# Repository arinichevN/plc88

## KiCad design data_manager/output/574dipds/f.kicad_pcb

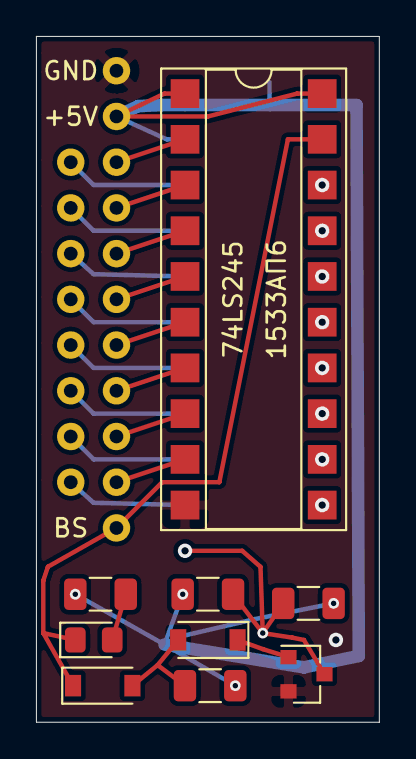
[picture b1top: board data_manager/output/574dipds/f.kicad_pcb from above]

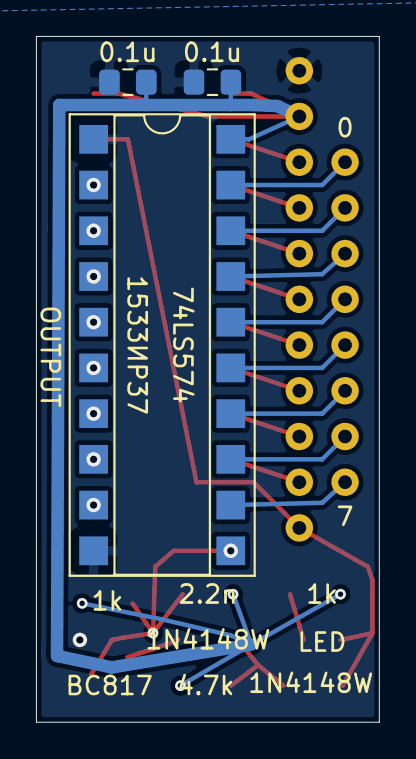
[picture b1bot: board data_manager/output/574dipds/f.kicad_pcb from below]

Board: 2 copper layers, 19.0 x 38.1 mm, 13 parts (3 on the bottom side), 31 nets.

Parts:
C1, C2: 0.1u; C_0805_2012Metric_Pad1.15x1.40mm_HandSolder
C3: 2.2n; C_1206_3216Metric
D1, D2: 1N4148W; D_SOD-123
D3: LED; LED_0805_2012Metric_Pad1.15x1.40mm_HandSolder
J1: data_manager_i; data_manager_im
Q1: BC817; SOT-23
R3: 4.7k; R_1206_3216Metric
R4, R5: 1k; R_1206_3216Metric
U1: 74LS245; DIP-20_W7.62mm_SMDSocket_SmallPads
U2: 74LS574; DIP-20_W7.62mm_SMDSocket_SmallPads

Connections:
+5V: C1.2, C2.2, C3.1, J1.18, R3.1, R4.1, R5.2, U1.1, U1.20, U2.20
BD0: U1.18, U2.2
BD1: U1.17, U2.3
BD2: U1.16, U2.4
BD3: U1.15, U2.5
BD4: U1.14, U2.6
BD5: U1.13, U2.7
BD6: U1.12, U2.8
BD7: U1.11, U2.9
BS: D1.1, D3.1, J1.19, U1.19
D0: J1.2, U1.2
D1: J1.4, U1.3
D2: J1.6, U1.4
D3: J1.8, U1.5
D4: J1.10, U1.6
D5: J1.12, U1.7
D6: J1.14, U1.8
D7: J1.16, U1.9
GND: C1.1, C2.1, J1.17, Q1.2, U1.10, U2.1, U2.10
unnamed: D1.2, D2.2, R3.2
unnamed: D2.1, Q1.1
unnamed: D3.2, R5.1
OPL0: J1.1, U2.19
OPL1: J1.3, U2.18
OPL2: J1.5, U2.17
OPL3: J1.7, U2.16
OPL4: J1.9, U2.15
OPL5: J1.11, U2.14
OPL6: J1.13, U2.13
OPL7: J1.15, U2.12
TCLK: C3.2, Q1.3, R4.2, U2.11

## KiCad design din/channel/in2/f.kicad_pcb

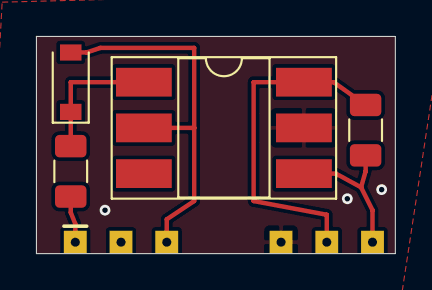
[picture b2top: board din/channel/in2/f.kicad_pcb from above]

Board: 2 copper layers, 19.9 x 12.1 mm, 5 parts (0 on the bottom side), 6 nets.

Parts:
D1: 1N4148W; D_SOD-123
J1: dio_channel_i; dio_channel_im
R1: 4.7k; R_1206_3216Metric
R2: 270; R_1206_3216Metric
U1: H11L1; DIP-6_W8.89mm_SMDSocket_LongPads

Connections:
+5V: J1.5, R2.2, U1.6
GND: J1.4, U1.5
IN: J1.1, R1.2
unnamed: D1.1, R1.1, U1.1
OUT: J1.6, R2.1, U1.4
VINM: D1.2, J1.3, U1.2

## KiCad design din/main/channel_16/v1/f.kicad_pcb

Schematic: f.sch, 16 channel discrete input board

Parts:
C1, C2: 0.1u; C_0805_2012Metric_Pad1.15x1.40mm_HandSolder
D1: SR1; LED_0805_2012Metric_Pad1.15x1.40mm_HandSolder
D2: SR0; LED_0805_2012Metric_Pad1.15x1.40mm_HandSolder
D3, D4, D5, D6, D7, D8, D9, D10, D11, D12, D13, D14, D15, D16, D17, D18: 1N4148W; D_SOD-123
J1: fm16_i; fm16_im
J2, J3: wrs_i
J4: bus_i; bus_im
J5: selector4_i
J6: power_+5V; power_i
R1, R2, R5, R6, R9, R10, R13, R14, R17, R18, R21, R22, R25, R26, R29, R30: 3.3k; R_1206_3216Metric_Pad1.42x1.75mm_HandSolder
R3, R4, R7, R8, R11, R12, R15, R16, R19, R20, R23, R24, R27, R28, R31, R32: 4.7k; R_1206_3216Metric_Pad1.42x1.75mm_HandSolder
R33, R34: 1k; R_1206_3216Metric_Pad1.42x1.75mm_HandSolder
U1, U2, U3, U4, U6, U7, U8, U9, U10, U11, U12, U13, U15, U16, U17, U18: LTV-357T; SO-4_4.4x3.6mm_P2.54mm
U21, U22: 74LS245; DIP-20_W8.89mm_SMDSocket_LongPads

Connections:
+5V: C1.2, C2.2, J2.6 (+5V), J3.6 (+5V), J5.1 (+5V), J6.2, R1.2, R2.2, R5.2, R6.2, R9.2, R10.2, R13.2, R14.2, R17.2, R18.2, R21.2, R22.2, R25.2, R26.2, R29.2, R30.2, R33.1, R34.1, U21.20 (VCC), U22.20 (VCC)
A0: J4.5 (A0), J5.2 (A0)
A1: J4.7 (A1), J5.3 (A1)
A2: J4.9 (A2), J5.4 (A2)
A3: J4.11 (A3), J5.5 (A3)
A4: J4.13 (A4), J5.6 (A4)
A5: J4.15 (A5), J5.7 (A5)
A6: J4.17 (A6), J5.8 (A6)
A7: J4.19 (A7), J5.9 (A7)
CLK: J4.21 (CLK), J4.22 (CLK), J5.10 (CLK)
D0: J4.6 (D0), U21.2 (A0), U22.2 (A0)
D1: J4.8 (D1), U21.3 (A1), U22.3 (A1)
D2: J4.10 (D2), U21.4 (A2), U22.4 (A2)
D3: J4.12 (D3), U21.5 (A3), U22.5 (A3)
D4: J4.14 (D4), U21.6 (A4), U22.6 (A4)
D5: J4.16 (D5), U21.7 (A5), U22.7 (A5)
D6: J4.18 (D6), U21.8 (A6), U22.8 (A6)
D7: J4.20 (D7), U21.9 (A7), U22.9 (A7)
GND: C1.1, C2.1, J1.21 (GND), J1.22 (GND), J1.23 (GND), J1.24 (GND), J1.25 (GND), J2.1 (GND), J3.1 (GND), J4.1 (GND), J4.2 (GND), J4.27 (GND), J4.28 (GND), J5.11 (GND), J6.3, U1.3, U2.3, U3.3, U4.3, U6.3, U7.3, U8.3, U9.3, U10.3, U11.3, U12.3, U13.3, U15.3, U16.3, U17.3, U18.3, U21.1 (A->B), U21.10 (GND), U22.1 (A->B), U22.10 (GND)
GND0_7: D3.2 (A), D4.2 (A), D5.2 (A), D6.2 (A), D7.2 (A), D8.2 (A), D9.2 (A), D10.2 (A), J1.17 (VM0_7), U1.2, U3.2, U6.2, U8.2, U10.2, U12.2, U15.2, U17.2
GND8_15: D11.2 (A), D12.2 (A), D13.2 (A), D14.2 (A), D15.2 (A), D16.2 (A), D17.2 (A), D18.2 (A), J1.20 (VM8_15), U2.2, U4.2, U7.2, U9.2, U11.2, U13.2, U16.2, U18.2
IN0: J1.1 (L0), R3.1
IN1: J1.2 (L1), R7.1
IN2: J1.3 (L2), R11.1
IN3: J1.4 (L3), R15.1
IN4: J1.5 (L4), R19.1
IN5: J1.6 (L5), R23.1
IN6: J1.7 (L6), R27.1
IN7: J1.8 (L7), R31.1
IN8: J1.9 (L8), R4.1
IN9: J1.10 (L9), R8.1
IN10: J1.11 (L10), R12.1
IN11: J1.12 (L11), R16.1
IN12: J1.13 (L12), R20.1
IN13: J1.14 (L13), R24.1
IN14: J1.15 (L14), R28.1
IN15: J1.16 (L15), R32.1
INL0: R1.1, U1.4, U21.18 (B0)
INL1: R5.1, U3.4, U21.17 (B1)
INL2: R9.1, U6.4, U21.16 (B2)
INL3: R13.1, U8.4, U21.15 (B3)
INL4: R17.1, U10.4, U21.14 (B4)
INL5: R21.1, U12.4, U21.13 (B5)
INL6: R25.1, U15.4, U21.12 (B6)
INL7: R29.1, U17.4, U21.11 (B7)
INL8: R2.1, U2.4, U22.18 (B0)
INL9: R6.1, U4.4, U22.17 (B1)
INL10: R10.1, U7.4, U22.16 (B2)
INL11: R14.1, U9.4, U22.15 (B3)
INL12: R18.1, U11.4, U22.14 (B4)
INL13: R22.1, U13.4, U22.13 (B5)
INL14: R26.1, U16.4, U22.12 (B6)
INL15: R30.1, U18.4, U22.11 (B7)
unnamed: D1.2 (A), R33.2
unnamed: D2.2 (A), R34.2
unnamed: D3.1 (K), R3.2, U1.1
unnamed: D4.1 (K), R7.2, U3.1
unnamed: D5.1 (K), R11.2, U6.1
unnamed: D6.1 (K), R15.2, U8.1
unnamed: D7.1 (K), R19.2, U10.1
unnamed: D8.1 (K), R23.2, U12.1
unnamed: D9.1 (K), R27.2, U15.1
unnamed: D10.1 (K), R31.2, U17.1
unnamed: D11.1 (K), R4.2, U2.1
unnamed: D12.1 (K), R8.2, U4.1
unnamed: D13.1 (K), R12.2, U7.1
unnamed: D14.1 (K), R16.2, U9.1
unnamed: D15.1 (K), R20.2, U11.1
unnamed: D16.1 (K), R24.2, U13.1
unnamed: D17.1 (K), R28.2, U16.1
unnamed: D18.1 (K), R32.2, U18.1
RD: J2.3 (WR), J3.3 (WR), J4.23 (RD)
S0: J2.4 (S), J5.12 (S0)
S1: J3.4 (S), J5.13 (S1)
SR0: D2.1 (K), J2.5 (SOUT), U21.19 (CE)
SR1: D1.1 (K), J3.5 (SOUT), U22.19 (CE)
VPBUS: J4.3 (+5V), J4.4 (+5V), J4.25 (+5V), J4.26 (+5V), J6.1
WR: J2.2 (WRN), J3.2 (WRN), J4.24 (WR)

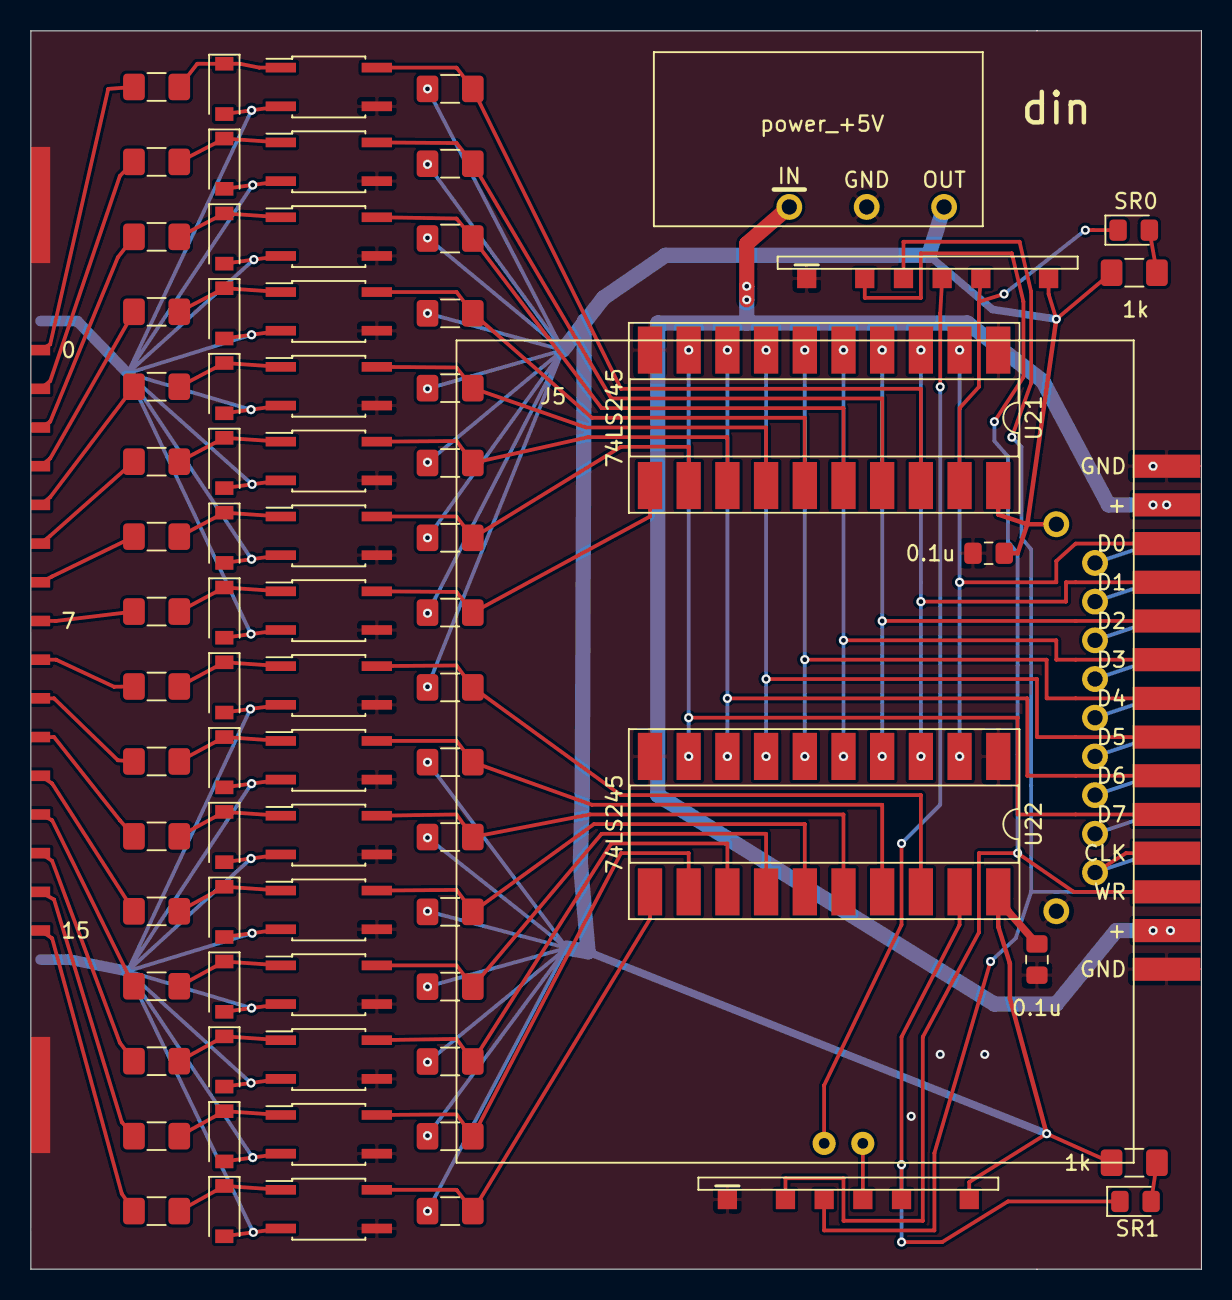
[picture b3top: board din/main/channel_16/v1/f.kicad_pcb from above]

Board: 2 copper layers, 76.8 x 81.3 mm, 78 parts (0 on the bottom side), 78 nets.

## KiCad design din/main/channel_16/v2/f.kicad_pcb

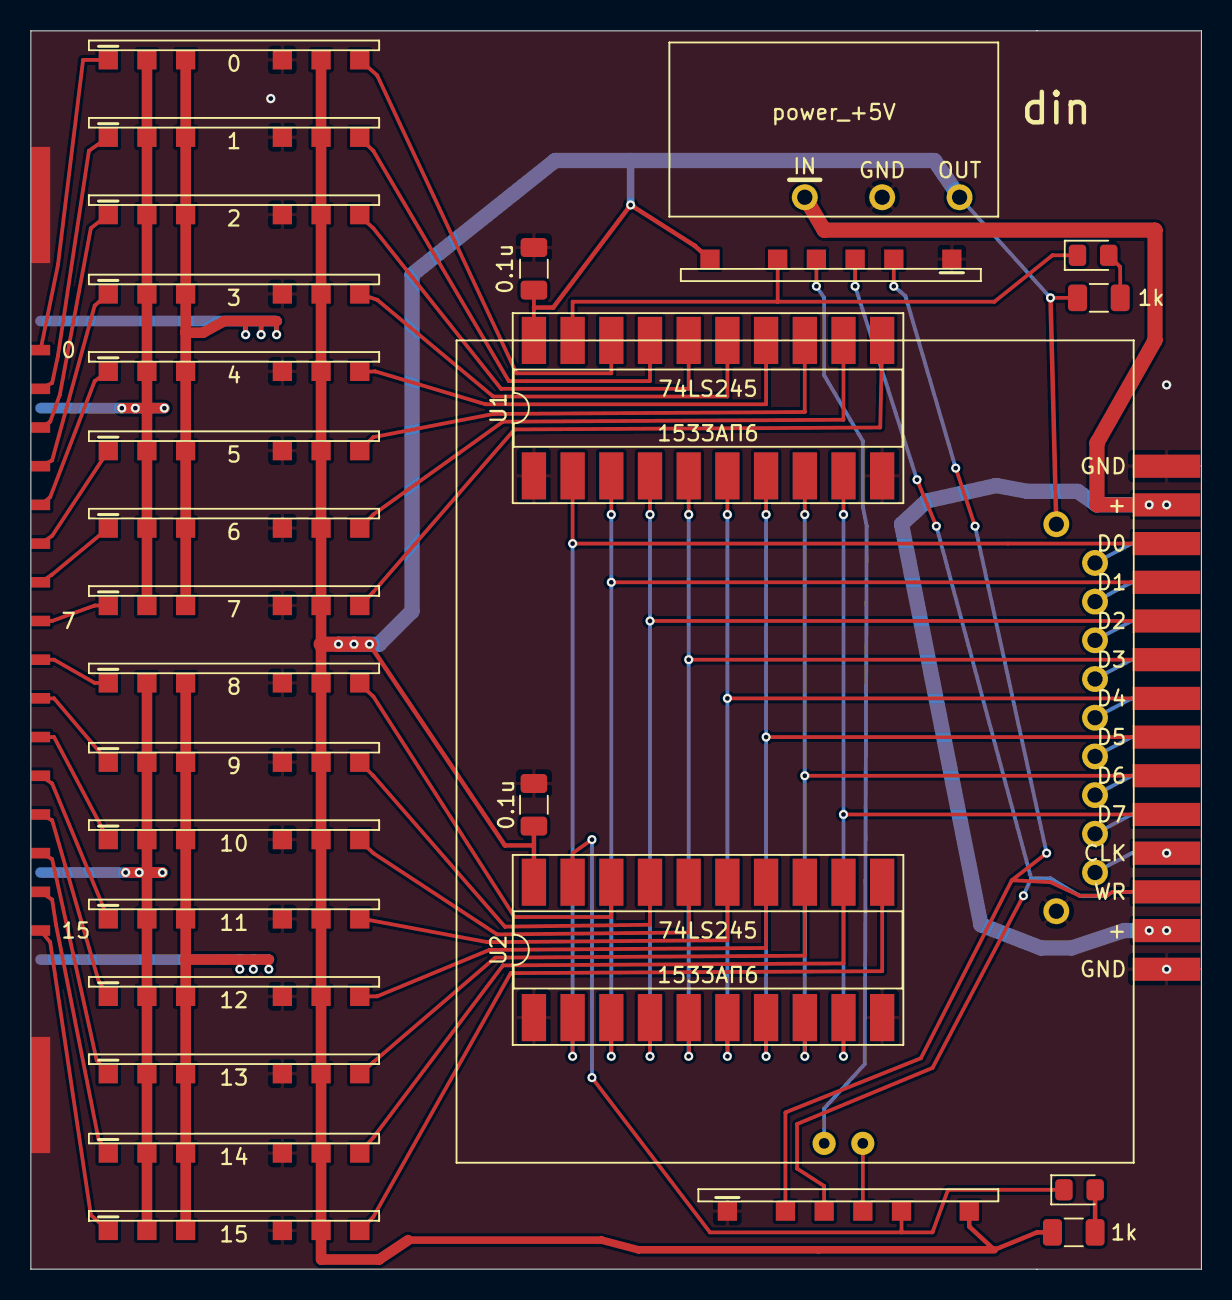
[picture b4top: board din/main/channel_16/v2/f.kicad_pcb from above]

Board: 2 copper layers, 76.8 x 81.3 mm, 30 parts (0 on the bottom side), 64 nets.

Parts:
C1, C2: 0.1u; C_1206_3216Metric
D1, D2: SR0; LED_0805_2012Metric_Pad1.15x1.40mm_HandSolder
J1: fm16_i; fm16_im
J2, J3, J4, J5, J6, J7, J8, J9, J13, J14, J15, J16, J17, J18, J19, J20: dio_channel_i
J10, J21: wrs_i
J11: selector4_i
J12: power_+5V; power_i
J22: bus_i; bus_im
R1, R2: 1k; R_1206_3216Metric
U1, U2: 74LS245; DIP-20_W8.89mm_SMDSocket_LongPads

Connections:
+5V: C1.2, C2.2, J2.5, J3.5, J4.5, J5.5, J6.5, J7.5, J8.5, J9.5, J10.6, J11.1, J12.2, J13.5, J14.5, J15.5, J16.5, J17.5, J18.5, J19.5, J20.5, J21.6, R1.1, R2.1, U1.20, U2.20
A0: J11.2, J22.5
A1: J11.3, J22.7
A2: J11.4, J22.9
A3: J11.5, J22.11
A4: J11.6, J22.13
A5: J11.7, J22.15
A6: J11.8, J22.17
A7: J11.9, J22.19
CLK: J11.10, J22.21, J22.22
D0: J22.6, U1.2, U2.2
D1: J22.8, U1.3, U2.3
D2: J22.10, U1.4, U2.4
D3: J22.12, U1.5, U2.5
D4: J22.14, U1.6, U2.6
D5: J22.16, U1.7, U2.7
D6: J22.18, U1.8, U2.8
D7: J22.20, U1.9, U2.9
GND: C1.1, C2.1, J1.21, J1.22, J1.23, J1.24, J1.25, J2.4, J3.4, J4.4, J5.4, J6.4, J7.4, J8.4, J9.4, J10.1, J11.11, J12.3, J13.4, J14.4, J15.4, J16.4, J17.4, J18.4, J19.4, J20.4, J21.1, J22.1, J22.2, J22.27, J22.28, U1.1, U1.10, U2.1, U2.10
GND0_7: J1.17, J2.3, J3.3, J4.3, J5.3, J6.3, J7.3, J8.3, J9.3
GND8_15: J1.20, J13.3, J14.3, J15.3, J16.3, J17.3, J18.3, J19.3, J20.3
IN0: J1.1, J2.1
IN1: J1.2, J3.1
IN2: J1.3, J4.1
IN3: J1.4, J5.1
IN4: J1.5, J6.1
IN5: J1.6, J7.1
IN6: J1.7, J8.1
IN7: J1.8, J9.1
IN8: J1.9, J13.1
IN9: J1.10, J14.1
IN10: J1.11, J15.1
IN11: J1.12, J16.1
IN12: J1.13, J17.1
IN13: J1.14, J18.1
IN14: J1.15, J19.1
IN15: J1.16, J20.1
INL0: J2.6, U1.18
INL1: J3.6, U1.17
INL2: J4.6, U1.16
INL3: J5.6, U1.15
INL4: J6.6, U1.14
INL5: J7.6, U1.13
INL6: J8.6, U1.12
INL7: J9.6, U1.11
INL8: J13.6, U2.18
INL9: J14.6, U2.17
INL10: J15.6, U2.16
INL11: J16.6, U2.15
INL12: J17.6, U2.14
INL13: J18.6, U2.13
INL14: J19.6, U2.12
INL15: J20.6, U2.11
unnamed: D1.2, R1.2
unnamed: D2.2, R2.2
RD: J10.3, J21.3, J22.23
S0: J10.4, J11.12
S1: J11.13, J21.4
SR0: D1.1, J10.5, U1.19
SR1: D2.1, J21.5, U2.19
V0_7: J1.18, J2.2, J3.2, J4.2, J5.2, J6.2, J7.2, J8.2, J9.2
V8_15: J1.19, J13.2, J14.2, J15.2, J16.2, J17.2, J18.2, J19.2, J20.2
VPBUS: J12.1, J22.3, J22.4, J22.25, J22.26
WR: J10.2, J21.2, J22.24

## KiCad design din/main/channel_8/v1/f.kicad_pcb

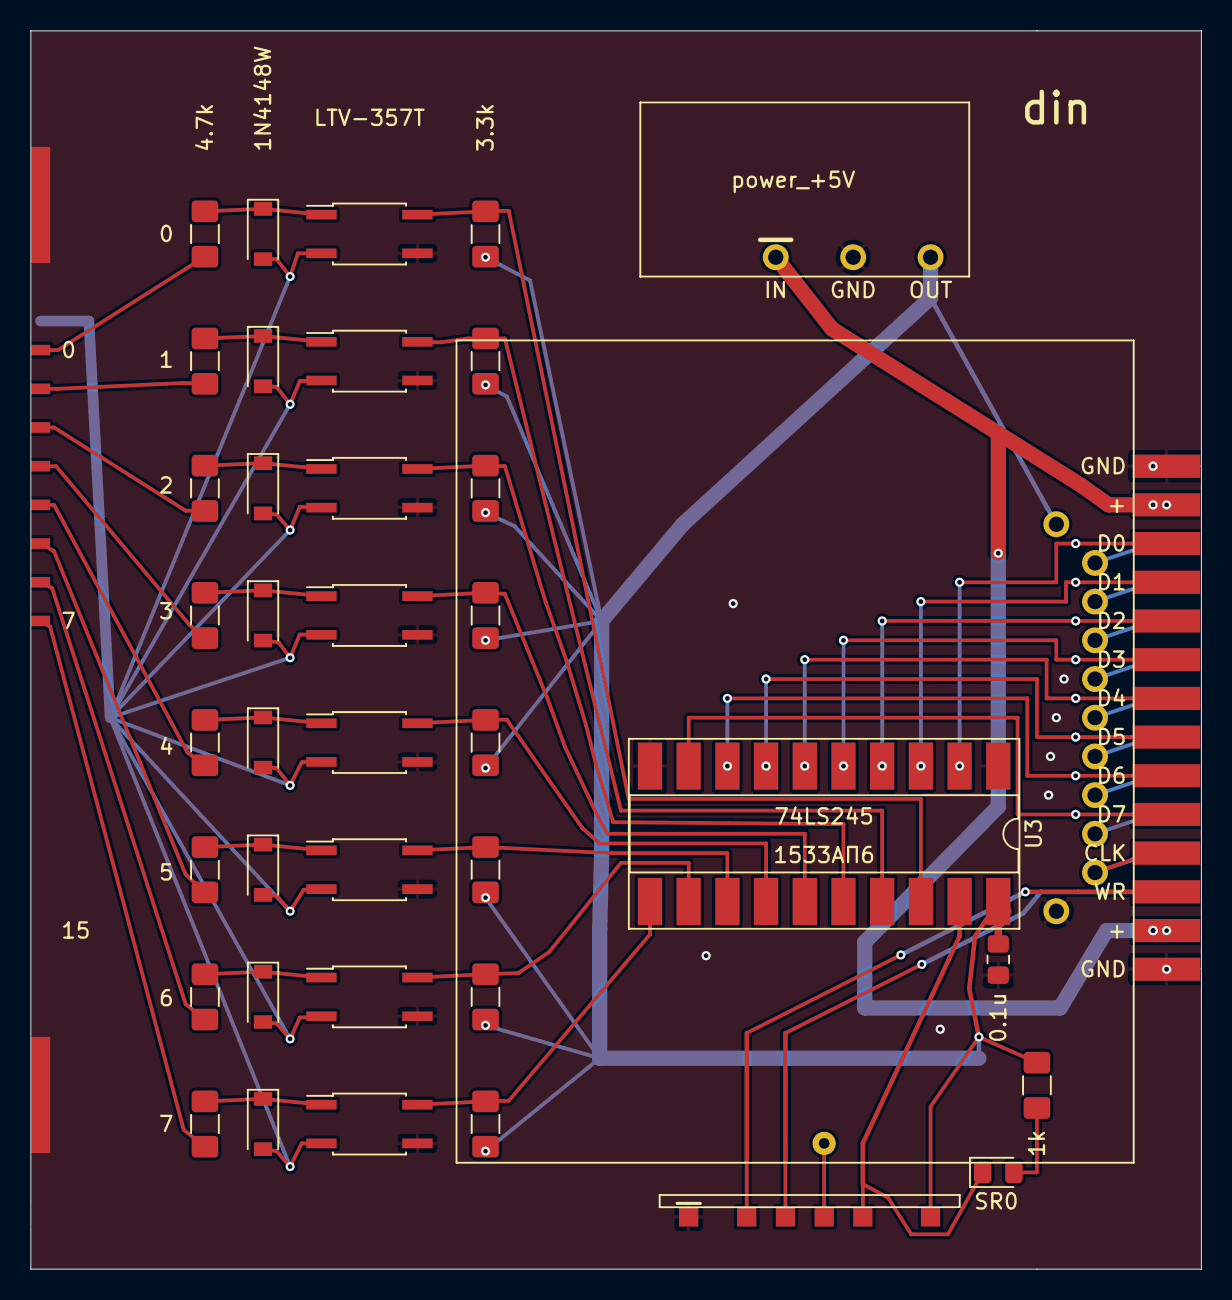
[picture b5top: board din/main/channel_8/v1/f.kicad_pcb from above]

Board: 2 copper layers, 76.8 x 81.3 mm, 41 parts (0 on the bottom side), 50 nets.

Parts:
C1: 0.1u; C_0805_2012Metric_Pad1.15x1.40mm_HandSolder
D1: SR0; LED_0805_2012Metric_Pad1.15x1.40mm_HandSolder
D2, D3, D4, D5, D6, D7, D8, D9: 1N4148W; D_SOD-123
J1: fm16_i; fm16_im
J2: bus_i; bus_im
J3: selector4_i
J4: power_+5V; power_i
J19: wrs_i
R1, R3, R5, R7, R9, R11, R13, R15: 3.3k; R_1206_3216Metric_Pad1.42x1.75mm_HandSolder
R2, R4, R6, R8, R10, R12, R14, R16: 4.7k; R_1206_3216Metric_Pad1.42x1.75mm_HandSolder
R17: 1k; R_1206_3216Metric_Pad1.42x1.75mm_HandSolder
U1, U2, U4, U5, U6, U7, U8, U9: LTV-357T; SO-4_4.4x3.6mm_P2.54mm
U3: 74LS245; DIP-20_W8.89mm_SMDSocket_LongPads

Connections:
+5V: C1.2, J3.1, J4.2, J19.6, R1.2, R3.2, R5.2, R7.2, R9.2, R11.2, R13.2, R15.2, R17.1, U3.20
A0: J2.5, J3.2
A1: J2.7, J3.3
A2: J2.9, J3.4
A3: J2.11, J3.5
A4: J2.13, J3.6
A5: J2.15, J3.7
A6: J2.17, J3.8
A7: J2.19, J3.9
CLK: J2.21, J2.22, J3.10
D0: J2.6, U3.2
D1: J2.8, U3.3
D2: J2.10, U3.4
D3: J2.12, U3.5
D4: J2.14, U3.6
D5: J2.16, U3.7
D6: J2.18, U3.8
D7: J2.20, U3.9
GND: C1.1, J1.21, J1.22, J1.23, J1.24, J1.25, J2.1, J2.2, J2.27, J2.28, J3.11, J4.3, J19.1, U1.3, U2.3, U3.1, U3.10, U4.3, U5.3, U6.3, U7.3, U8.3, U9.3
GND0_7: D2.2, D3.2, D4.2, D5.2, D6.2, D7.2, D8.2, D9.2, J1.17, U1.2, U2.2, U4.2, U5.2, U6.2, U7.2, U8.2, U9.2
IN0: J1.1, R2.1
IN1: J1.2, R4.1
IN2: J1.3, R6.1
IN3: J1.4, R8.1
IN4: J1.5, R10.1
IN5: J1.6, R12.1
IN6: J1.7, R14.1
IN7: J1.8, R16.1
INL0: R1.1, U1.4, U3.18
INL1: R3.1, U2.4, U3.17
INL2: R5.1, U3.16, U4.4
INL3: R7.1, U3.15, U5.4
INL4: R9.1, U3.14, U6.4
INL5: R11.1, U3.13, U7.4
INL6: R13.1, U3.12, U8.4
INL7: R15.1, U3.11, U9.4
unnamed: D1.2, R17.2
unnamed: D2.1, R2.2, U1.1
unnamed: D3.1, R4.2, U2.1
unnamed: D4.1, R6.2, U4.1
unnamed: D5.1, R8.2, U5.1
unnamed: D6.1, R10.2, U6.1
unnamed: D7.1, R12.2, U7.1
unnamed: D8.1, R14.2, U8.1
unnamed: D9.1, R16.2, U9.1
RD: J2.23, J19.3
S0: J3.12, J19.4
SR0: D1.1, J19.5, U3.19
VPBUS: J2.3, J2.4, J2.25, J2.26, J4.1
WR: J2.24, J19.2

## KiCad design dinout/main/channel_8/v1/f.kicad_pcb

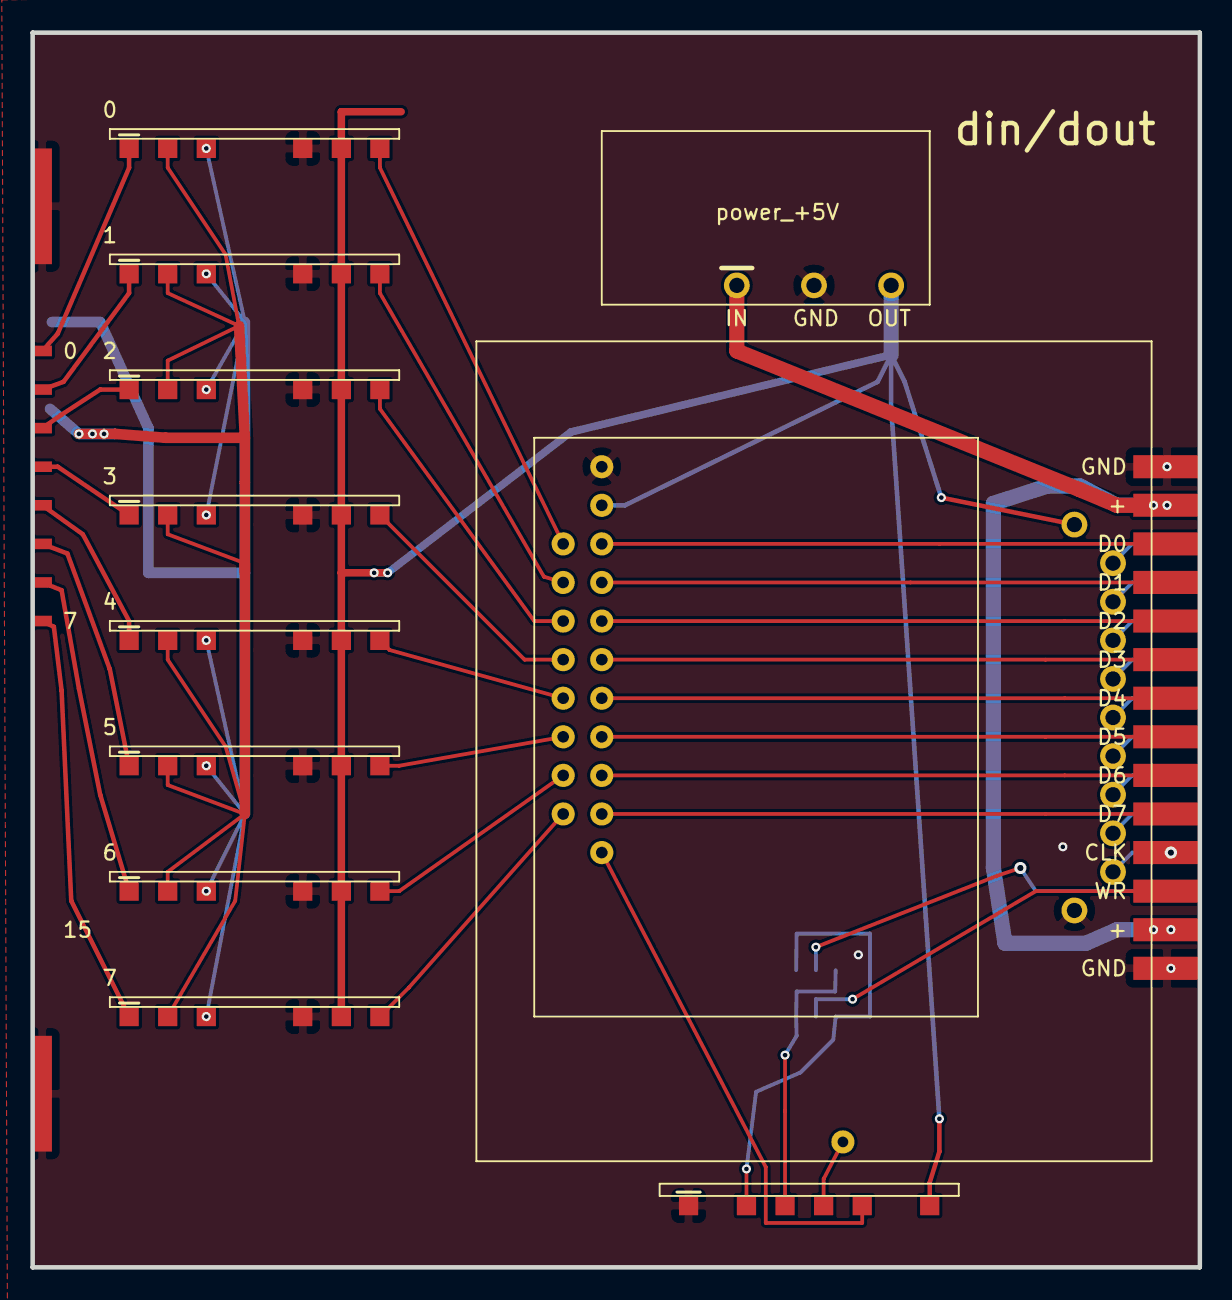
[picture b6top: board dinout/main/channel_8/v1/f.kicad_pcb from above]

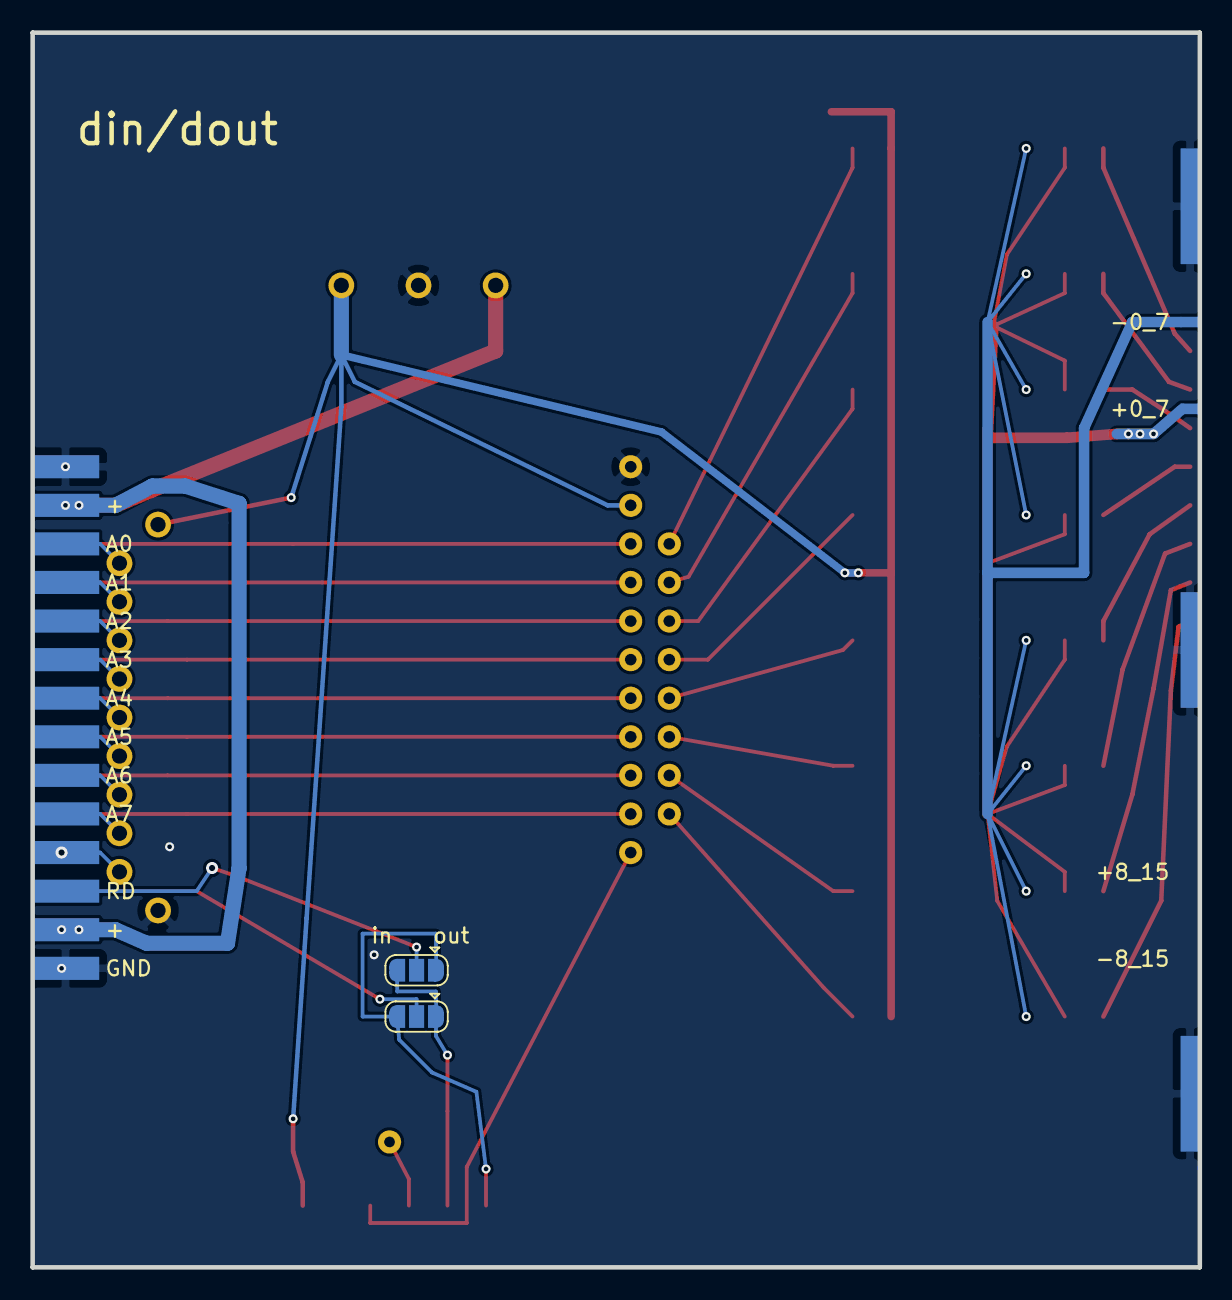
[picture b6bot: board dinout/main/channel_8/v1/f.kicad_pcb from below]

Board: 2 copper layers, 76.8 x 81.3 mm, 16 parts (2 on the bottom side), 44 nets.

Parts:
J1: fm16_i; fm16_im
J2: 0; dio_channel_i
J3: 1; dio_channel_i
J4: 2; dio_channel_i
J5: 3; dio_channel_i
J6: 4; dio_channel_i
J7: 5; dio_channel_i
J8: 6; dio_channel_i
J9: 7; dio_channel_i
J10: data_manager_i
J11: wrs_i
J12: selector4_i
J13: bus_i; bus_im
J14: power_+5V; power_i
JP1, JP2: Jumper_3_Open; SolderJumper-3_P1.3mm_Open_RoundedPad1.0x1.5mm

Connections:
+5V: J2.5, J3.5, J4.5, J5.5, J6.5, J7.5, J8.5, J9.5, J10.18, J11.6, J12.1, J14.2
A0: J12.2, J13.5
A1: J12.3, J13.7
A2: J12.4, J13.9
A3: J12.5, J13.11
A4: J12.6, J13.13
A5: J12.7, J13.15
A6: J12.8, J13.17
A7: J12.9, J13.19
CLK: J12.10, J13.21, J13.22
D0: J10.2, J13.6
D1: J10.4, J13.8
D2: J10.6, J13.10
D3: J10.8, J13.12
D4: J10.10, J13.14
D5: J10.12, J13.16
D6: J10.14, J13.18
D7: J10.16, J13.20
GND: J1.21, J1.22, J1.23, J1.24, J1.25, J2.4, J3.4, J4.4, J5.4, J6.4, J7.4, J8.4, J9.4, J10.17, J11.1, J12.11, J13.1, J13.2, J13.27, J13.28, J14.3
NO: J11.2, JP1.1, JP2.3
OPL0: J2.6, J10.1
OPL1: J3.6, J10.3
OPL2: J4.6, J10.5
OPL3: J5.6, J10.7
OPL4: J6.6, J10.9
OPL5: J7.6, J10.11
OPL6: J8.6, J10.13
OPL7: J9.6, J10.15
OUT0: J1.1, J2.1
OUT1: J1.2, J3.1
OUT2: J1.3, J4.1
OUT3: J1.4, J5.1
OUT4: J1.5, J6.1
OUT5: J1.6, J7.1
OUT6: J1.7, J8.1
OUT7: J1.8, J9.1
RD: J13.23, JP1.2
S0: J11.4, J12.12
SW0: J10.19, J11.5
VM0_7: J1.17, J2.3, J3.3, J4.3, J5.3, J6.3, J7.3, J8.3, J9.3
VP0_7: J1.18, J2.2, J3.2, J4.2, J5.2, J6.2, J7.2, J8.2, J9.2
VPBUS: J13.3, J13.4, J13.25, J13.26, J14.1
WR: J13.24, JP2.2
YES: J11.3, JP1.3, JP2.1
